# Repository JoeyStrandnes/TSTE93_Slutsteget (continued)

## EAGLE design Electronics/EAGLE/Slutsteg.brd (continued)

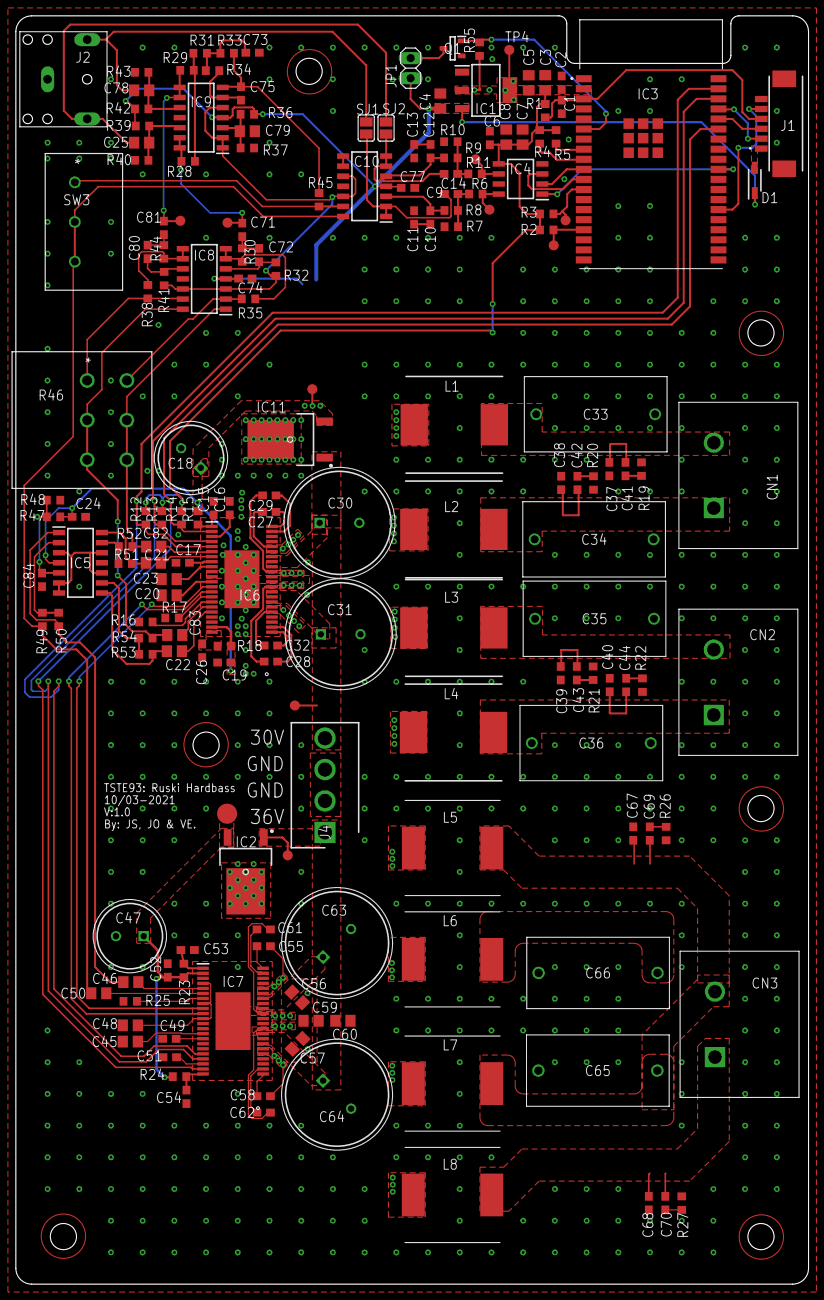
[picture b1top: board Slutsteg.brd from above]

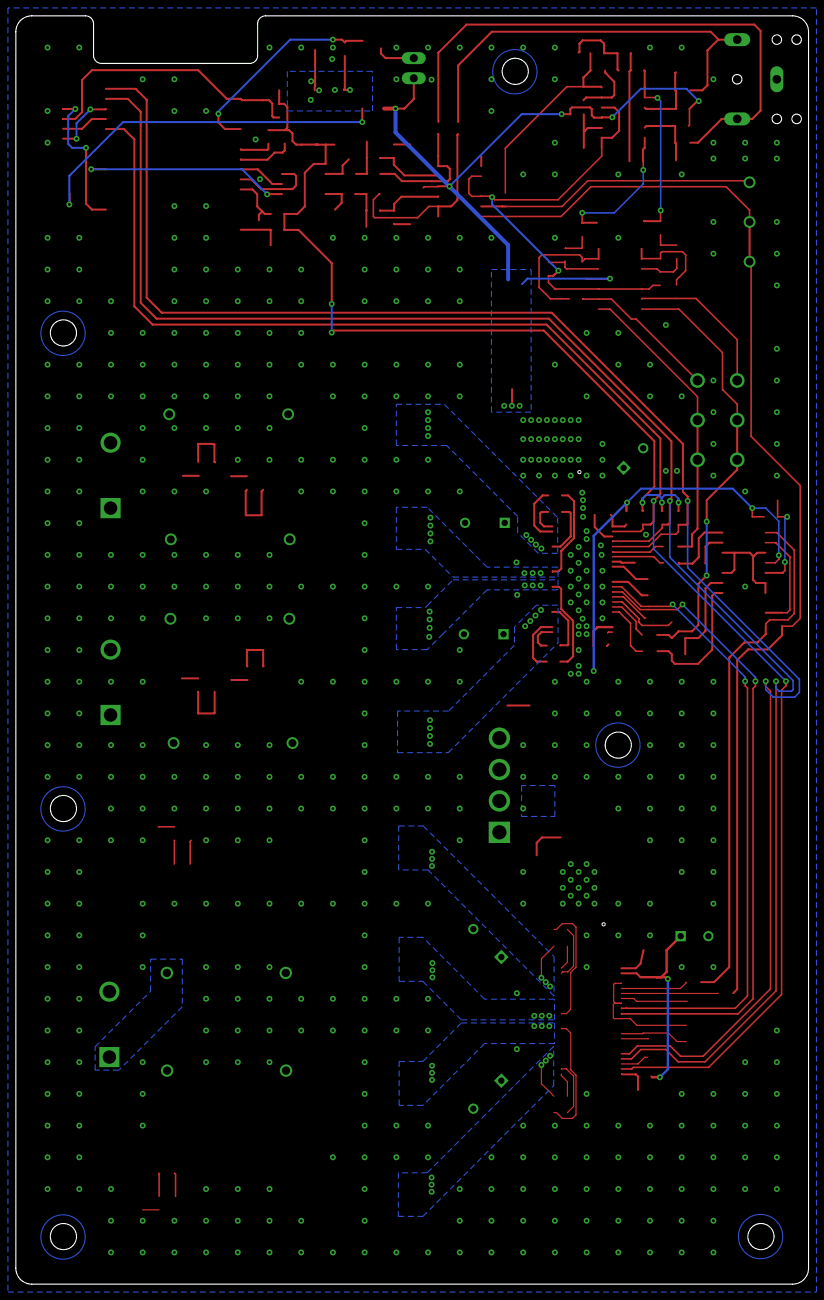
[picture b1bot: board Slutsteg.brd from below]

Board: 2 copper layers, 100.0 x 160.0 mm, 184 parts (2 on the bottom side), 117 nets.

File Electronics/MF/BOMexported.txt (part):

Partlist exported from D:/GitHub/TSTE93_Slutsteget/Electronics/EAGLE/Slutsteg.sch at 2021-03-10 17:28

Qty Value               Device                 Package                        Parts                                                                                          Description                                                                                                                   ARROW_PART_NUMBER  ARROW_PRICE-STOCK                                                    BUILT_BY COPYRIGHT                                                   DATASHEET                                                                                                                                          DESCRIPTION                                                                                                                   HEIGHT MANUFACTURER_NAME                MANUFACTURER_PART_NUMBER MOUSER_PART_NUMBER   MOUSER_PRICE-STOCK                                                                                            POPULARITY SOURCELIBRARY                 SPICEPREFIX TP_SIGNAL_NAME VENDOR            
2                       SJ                     SJ                             SJ1, SJ2                                                                                       SMD solder JUMPER                                                                                                                                                                                                                                                                                                                                                                                                                                                                                                                                                                                                                                                                                                                                                               33                                                                                    
1   0532610671          0532610671             0532610671                     J1                                                                                             1.25mm Pitch PicoBlade Header, Surface Mount, Right Angle, 6 Circuits                                                         0532610671         https://www.arrow.com/en/products/0532610671/molex                                                                                                                                                                                                                                           1.25mm Pitch PicoBlade Header, Surface Mount, Right Angle, 6 Circuits                                                         mm     Molex                            0532610671                                                                                                                                                                                                                                        
12  100K/5%/0.1W        R-EU_R0603             R0603                          R36, R37, R39, R40, R42, R43, R47, R48, R51, R52, R53, R54                                     RESISTOR, European symbol                                                                                                                                                                                                                                                                                                                                                                                                                                                                                                                                                                                                                                                                                                                                                       70                                       R                                            
19  100nF/50V           C-EUC0603              C0603                          C1, C2, C6, C15, C16, C19, C24, C26, C51, C52, C53, C54, C71, C72, C74, C77, C80, C81, C84     CAPACITOR, European symbol                                                                                                                                                                                                                                                                                                                                                                                                                                                                                                                                                                                                                                                                                                                                                      73                                       C                                            
21  10K/5%/0.1W         R-EU_R0603             R0603                          R1, R2, R3, R4, R5, R6, R7, R8, R9, R10, R11, R30, R32, R34, R35, R38, R41, R44, R45, R49, R50 RESISTOR, European symbol                                                                                                                                                                                                                                                                                                                                                                                                                                                                                                                                                                                                                                                                                                                                                       70                                       R                                            
8   10nF/50V            C-EUC0603              C0603                          C17, C41, C42, C43, C44, C49, C69, C70                                                         CAPACITOR, European symbol                                                                                                                                                                                                                                                                                                                                                                                                                                                                                                                                                                                                                                                                                                                                                      73                                       C                                            
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
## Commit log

2021-01-21 Added a temporary overview
2021-01-21 Added Block diagram and datasheets
2021-01-21 Added connector reset line. System will be powered down if no cable is attached
2021-01-29 Länkar till Högtalarnas frekvgång
2021-01-29 Added datasheets and info regarding the speaker elements.
2021-01-29 Updated block diagram
2021-02-04 Test schematic
2021-02-04 Fixed name
2021-02-04 Fixed folder
2021-02-04 Minor name change
2021-02-04 test me opamp
    test med opamp
2021-02-04 Test-Coop
2021-02-04 Removed test componens
2021-02-04 Lade till Hierachy block delningsfilter
2021-02-04 Diverse efter labben
2021-02-08 Added an Eagle design block for TPA3244
2021-02-08 Laddade upp delningsfilter
2021-02-08 Länkade delningsfilter i huvudfilen
2021-02-09 Renamed folder and added entries to .gitignore
2021-02-11 FIxed name, im retarded
2021-02-11 Might be done with the schematic
2021-02-11 Exported all used components to one library file
2021-02-11 Flyttat teorimappen och lagt till lite dokument om filter
2021-02-12 testar eagle :D
2021-02-17 gjort om delningsfilter till MFB, verkar funka
2021-02-18 Added the TPA3244 design block to the schematic and updated the coils.
2021-02-18 Temporary layout to see the size of the card.
2021-02-18 Minor changes to the layout
2021-02-18 TPA3251 design block
    cool beans
2021-02-18 Fixed minor issues with TPA3251 design block and added it to the schematic.
2021-02-18 Fixed missing page.
2021-02-18 Börjat med eagle på delningsfiltret (MFB)
2021-02-24 Fixed issues with the original schematic. No ERC errors!
2021-02-24 Added example files for a F-6888 BLE module
2021-02-24 Added Software for ESP32 BLE audio sink.
2021-02-24 Changed value of main bulk capacitors to the 1000uF version of the same capacitor
2021-02-24 Changed capacitor size to match the TPA3251 design. Changed bulk capacitors to 1000uF to match TPA3251.
2021-02-24 Added schematics
2021-02-24 Updated the schematic with the new designblocks
2021-02-24 Helt nytt filter typ
    Lagt till stereo-ingång som helt ahde missats innan. SUmmator för basen som summerar Vänster/Höger.
    Ska färdigställa volymknobb
2021-02-25 Ändrat HP-filtrerna till Sallen-Key
    Lagt till volymändring och ändrat HP-filtrerna till Sallen-Key (igen) pga nån snubbe https://sound-au.com/articles/active-filters.htm
2021-02-25 Gjort färdigt filter och lagt till komponentvärden
2021-02-25 Tog bort onödiga filer
2021-02-26 Changed to the internal regulator would not drive the pullups. External 3.3V DC/DC is needed
2021-02-26 Did the layout for TPA3244 and added 3D-models for those components
2021-02-26 Preliminary processor configuration
2021-02-26 Added the ESP32 board and placed it in the layout.
2021-02-26 Added speaker connector models.
2021-03-01 Cleaned up the main file.
2021-03-04 Lagt till avkoppling-caps på opamp railen
2021-03-04 Sammanfogat design blocks
2021-03-04 Minor changes to ESP32 implementation
2021-03-04 Renumbered components.
2021-03-04 Updated components value
2021-03-04 Changed some component footprints and simplified the V-Reg configuration
2021-03-04 Changed OP-AMP for the DAC
2021-03-04 Changed footprints for caps
2021-03-04 Changed components
2021-03-04 Lagt till 3.5mm connector
2021-03-04 Revert "Lagt till 3.5mm connector"
    This reverts commit b586c7d4102b99b6a6c1c70b6fd3026c9e3e15a7.
2021-03-04 Lagt till 3.5mm input och vridpot för Basen
2021-03-04 FIxat lite kondensatorer
    :)
2021-03-04 Fixa en sista kondensator
    :DDDDDDD
2021-03-04 En halvdan bom
    Enbart länkar än så länge
2021-03-04 added 240V connector
2021-03-04 Added some more 240V stuff
2021-03-04 more stuffs
2021-03-04 Snyggat till kopplingar
2021-03-06 fixade lite graj
2021-03-06 Börjat med TPA3251s del av kretskortet
2021-03-06 Added dual pot library
2021-03-06 Lagt till double-gang pot och petat lite i layouten
2021-03-06 Continued with layout and fixed minor issues with the schematic.
2021-03-07 ALmost done with the ESP32 & TPA3244 layout
2021-03-08 Lagt till artikelnummer och inköpsantal
2021-03-08 Uppdaterad och skickad till Arta
    Skickad de poster som var till ELFA och RS. Uppdaterad nya kolumner för inköp med marginal. Måste göra klart de vi köper själva från Digikey
2021-03-08 started on the smaller components
2021-03-08 PCB-layout: dragit till första opampstegen
2021-03-08 Lagt till mer rader i BOMEN
2021-03-08 Connected more things in the layout. Added a heatsink and lib file for it.
2021-03-09 Reduced I2C bit size in bitstream from 24-16.
2021-03-09 small tweaks
2021-03-09 PANIC, lagt till extra OP
    Kör DIFF input på alla klass D
2021-03-09 Cleaned up TPA3251
2021-03-09 Uppdaterat lite extra poster
2021-03-09 Almost done with first draft of layout.
2021-03-09 First draft of layout is finished. No DRC warnings.
2021-03-09 fixade stavfel i BOM
2021-03-09 Added some test points. More to come....
2021-03-09 TPs och Viastiching
    TP,VIAstich,borrhål
2021-03-10 Moved labels in layout.
2021-03-10 Finished the first draft and exported the Gerber files.
2021-03-10 text-BOM
2021-03-10 Added a header for the cooling fan.
2021-03-12 Pillar lite med ny BOM
    Fortfarande lite rörigt
2021-05-02 Added housing for the electronics and PSU.
2021-05-03 Added project images
2021-05-03 Added images
2021-05-09 Added frequency response of the speaker
2021-05-09 Added smoothing script for AudMeS plots
2021-05-11 Added images for magnitude response
2021-05-12 Lite bilder och uppsnyggning i Multisimfilen
2021-05-12 Mer bild-hantering
2021-05-13 A final render of the board
    Much cool! Very wow!
2021-05-19 Added schematic
2021-05-20 Added presentation PDF
